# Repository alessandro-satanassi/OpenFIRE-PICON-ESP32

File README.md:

# OpenFIRE-PICON-AS-ESP32
Lightgun PICON-AS for OpenFIRE-ESP32
https://alessandro-satanassi.github.io/OpenFIRE-PICON-AS-ESP32/

PICON-AS (nome del progetto: OpenFIRE-PICON-AS-ESP32) è una lightgun derivata dal modello PICON-OG di ICON che nasce per essere utilizzata in modalità completamente WIRELESS; la sua caratteristica distintiva è infatti la capacità di funzionare interamente a batteria, senza la necessità di alcun cavo di collegamento, garantendo una libertà di movimento assoluta anche durante l’uso del rinculo mediante solenoide. Rispetto al progetto originale, da cui riprende la struttura e l'hardware, la maggior parte dei componenti (inclusi molti file .STL) è identica, ma la periferica è stata adattata per semplificare i collegamenti elettrici e supportare appieno la gestione wireless. Per utilizzare tale connessione senza fili, è necessario collegare un dongle wireless a una porta USB del PC (vedi sezione Hardware).

Il cuore del sistema è una cella Li-ion 21700 ricaricabile e non rimovibile, gestita da un hardware di ricarica integrato direttamente nel dispositivo. Per la massima versatilità, la periferica dispone di un ingresso USB-C utile sia per rigenerare la carica sia per l'utilizzo cablato su PC, oltre a un jack per alimentazione esterna a 12V; quest'ultimo permette di azionare solenoide e circuiti preservando la batteria e ricaricandola simultaneamente. La dotazione comprende un interruttore di accensione generale, uno switch dedicato per disattivare il rinculo e un indicatore LED per il monitoraggio del livello di carica.

PICON-AS supporta numerose funzionalità, tra cui rumble, rinculo con solenoide, display OLED, LED Neopixel, joystick analogico, D-PAD, pulsanti START, SELECT, A,B,C e switch a pompa. N.B. Sebbene il sistema sia compatibile con tutte queste feature, l'installazione della maggior parte di esse rimane opzionale e a discrezione dell'utente.

A livello software, la lightgun è compatibile con il firmware originale per RP2040, ma le funzionalità aggiuntive sono disponibili solo utilizzando un microcontrollore ESP32-S3 con il firmware OpenFIRE-firmware-ESP32 (vedi sezione Hardware). Questo firmware per ESP32 è un porting del firmware originale (con cui mantiene piena compatibilità), al quale sono state apportate solo poche modifiche e l’aggiunta del supporto wireless. Si ringraziano gli autori dei progetti originali PICON-OG e OpenFIRE per il lavoro su cui si basa questo progetto.

===============================================================
Lightgun PICON-AS for OpenFIRE-ESP32
https://alessandro-satanassi.github.io/OpenFIRE-PICON-AS-ESP32/

PICON-AS (project name: OpenFIRE-PICON-AS-ESP32) is a lightgun derived from ICON's PICON-OG model, designed to be used in a completely WIRELESS mode; its distinctive feature is indeed the ability to operate entirely on battery power, without the need for any connecting cables, ensuring absolute freedom of movement even when using the solenoid recoil. Compared to the original project, from which it inherits the structure and hardware, most of the components (including many .STL files) are identical, but the peripheral has been adapted to simplify the electrical connections and fully support wireless management. To use this wireless connection, a wireless dongle must be connected to a USB port on the PC (see the Hardware section).

The heart of the system is a rechargeable and non-removable 21700 Li-ion cell, managed by charging hardware integrated directly into the device. For maximum versatility, the peripheral features a USB-C input, which is useful both for recharging and for wired use on a PC, as well as a 12V external power jack. The latter allows the solenoid and circuits to be operated while preserving the battery and charging it simultaneously. The equipment includes a main power switch, a dedicated switch to disable the recoil, and a LED indicator to monitor the charge level.

PICON-AS supports numerous features, including rumble, solenoid recoil, OLED display, Neopixel LEDs, analog joystick, D-PAD, START, SELECT, A, B, C buttons, and a pump-action switch. N.B. Although the system is compatible with all these features, the installation of most of them remains optional and at the user's discretion.

On the software side, the lightgun is compatible with the original firmware for RP2040, but the additional features are only available by using an ESP32-S3 microcontroller with the OpenFIRE-firmware-ESP32 firmware (see the Hardware section). This ESP32 firmware is a port of the original firmware (with which it maintains full compatibility), to which only a few modifications and the addition of wireless support have been made. Special thanks go to the authors of the original PICON-OG and OpenFIRE projects for the work on which this project is based.

============================================

OpenFIRE-PICON-ESP32 è un progetto derivato da Picon-OG, creato da iCON.  
Questa opera è distribuita sotto licenza Creative Commons Attribution-NonCommercial-ShareAlike 4.0 International (CC BY-NC-SA 4.0), come il progetto da cui è derivato.

================== licenza ===================================
https://creativecommons.org/share-your-work/cclicenses/
CC BY-NC-SA
This license enables reusers to distribute, remix, adapt, and build upon the material in any medium or format for noncommercial purposes only, and only so long as attribution is given to the creator. If you remix, adapt, or build upon the material, you must license the modified material under identical terms. CC BY-NC-SA includes the following elements:

 BY: credit must be given to the creator.
 NC: Only noncommercial uses of the work are permitted.
 SA: Adaptations must be shared under the same terms.
==============================================================

Il progetto Picon-OG
================================================================================================
https://diylightgun.com/lightgun-details/?lgid=506
============================================================
PiCON-OG
3D Printed Lightgun by iCON

Smaller, lighter version of the iCON featuring a sliding recoil, rumble motor, pump reload, analog joystick, 5-way navigation, OLED display, NeoPixel LED in back, accelerometer, screw in wide angle or fish eye lens connection. All parts (including the one-piece frame) can be printed on an Ender 3. The OLED, NeoPixel LED, accelerometer and analog joystick will only work with OpenFIRE firmware running on a Raspberry Pi RP2040 based microcontroller (Pico, Pico W, RP2040 Zero).

The author marked this model as their own original creation.
This work is licensed under a CC BY-NC-SA Creative Commons (4.0 International License)
================================================================================================

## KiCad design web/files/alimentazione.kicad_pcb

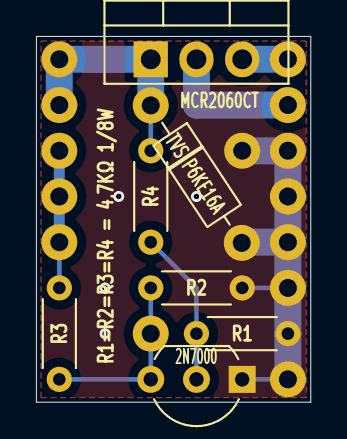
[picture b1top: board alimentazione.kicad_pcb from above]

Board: 2 copper layers, 15.2 x 20.3 mm, 7 parts (0 on the bottom side), 4 nets.

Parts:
2N7000: TO-92_Inline_Wide
MCR2060CT: TO-220-3_Vertical
R1: R1; R_Axial_DIN0204_L3.6mm_D1.6mm_P5.08mm_Horizontal
R2: R2; R_Axial_DIN0204_L3.6mm_D1.6mm_P5.08mm_Horizontal
R3: R3; R_Axial_DIN0204_L3.6mm_D1.6mm_P5.08mm_Horizontal
R4: R4; R_Axial_DIN0204_L3.6mm_D1.6mm_P5.08mm_Horizontal
TVS P6KE16A: D_DO-41_SOD81_P9.158mm_Horizontal

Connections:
12V_EXTERN: MCR2060CT.1, R4.2, TVS P6KE16A.1
EN_BOOSTER: 2N7000.3, R2.1, R3.1
GATE_CONTROL_12V: 2N7000.2, R1.1, R4.1
GND: 2N7000.1, R1.2, R2.2, TVS P6KE16A.2

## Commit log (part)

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2025-09-09 inserimento file originali di picon-og e file di lavoro del progetto dalla versione 12
    inserimento file originali di picon-og e file di lavoro del progetto dalla versione 12
2025-09-11 nuove versioni
2025-09-20 aggiornamento e utilità
2025-09-21 aggiunto progetto kicad
2025-09-22 NUOVA VERSIONE MILLEFORI
2025-09-30 prima versione di stampa
2025-09-30 INSERIMENTO RP2040 - ESP32 PICO
2025-10-02 INSERIMENTO_IMMAGINI_ E PROGETTI KIKAD
2025-10-04 sito web
2026-02-08 agg sez. software
2026-02-08 agg home
2026-02-13 aggiornamento
2026-02-14 aggiornamento sito
2026-02-14 AGG SITO
2026-02-21 inserito power-path
2026-02-21 aggiunto driver solenoide
2026-02-22 aggiunte alcune board da completare
2026-02-23 AGG SOLENOIDE E CAM
2026-02-25 ins OLED
2026-03-09 aggiornamento file freecad - VERSIONE DEFINITIVA WIRELESS CON SWITCH GROSSI
2026-03-11 inserimento istruzioni switch
2026-03-11 correzioni varie
2026-03-12 agg. RUMBLE e step-down
2026-03-12 agg. jack 12v
2026-03-12 agg. stl
2026-03-12 agg homepage
2026-03-28 agg cam
2026-05-05 AGGIORNAMENTO SITO .. INIZIO INTRODUZIONE PEDALE, INSERIMENTO FILE GERBER, VARIE
2026-05-06 agg inserimento file kicad
2026-05-23 agg img
2026-06-11 agg doc
2026-06-12 aggiunti file freecad
